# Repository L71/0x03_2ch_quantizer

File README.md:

0x03 2ch Quantizer
==================

This thing is a two channel CV quantizer for Eurorack, intended to make sure
some oscillators played by an analog sequencer are actually playing in tune :)

* two CV input channels, each input 0-5V is mapped to output 0-4.096V, four octaves @ 1V/oct.
* transpose knob per channel, +/- 1 octave in semitone steps
* The green LEDs will be brighter when transpose is set to -12/0/+12 half notes
* Red LED lights up if any channel tries to go off limits

Prototype build for Eurorack (complete with panel) was OK :) 

The microcontroller source code is released under the GPL v3.0 license. 
The PCBs and front panel drawings are released under the Creative Commons CC-BY-SA 4.0 license.

Tools used, all on MacOS 10.10:
C compiler: avr-gcc 4.3.3, http://www.obdev.at/products/crosspack/index.html
PCB: Eagle 7.1, www.cadsoftusa.com
Panel: Inkscape 0.91, inkscape.org

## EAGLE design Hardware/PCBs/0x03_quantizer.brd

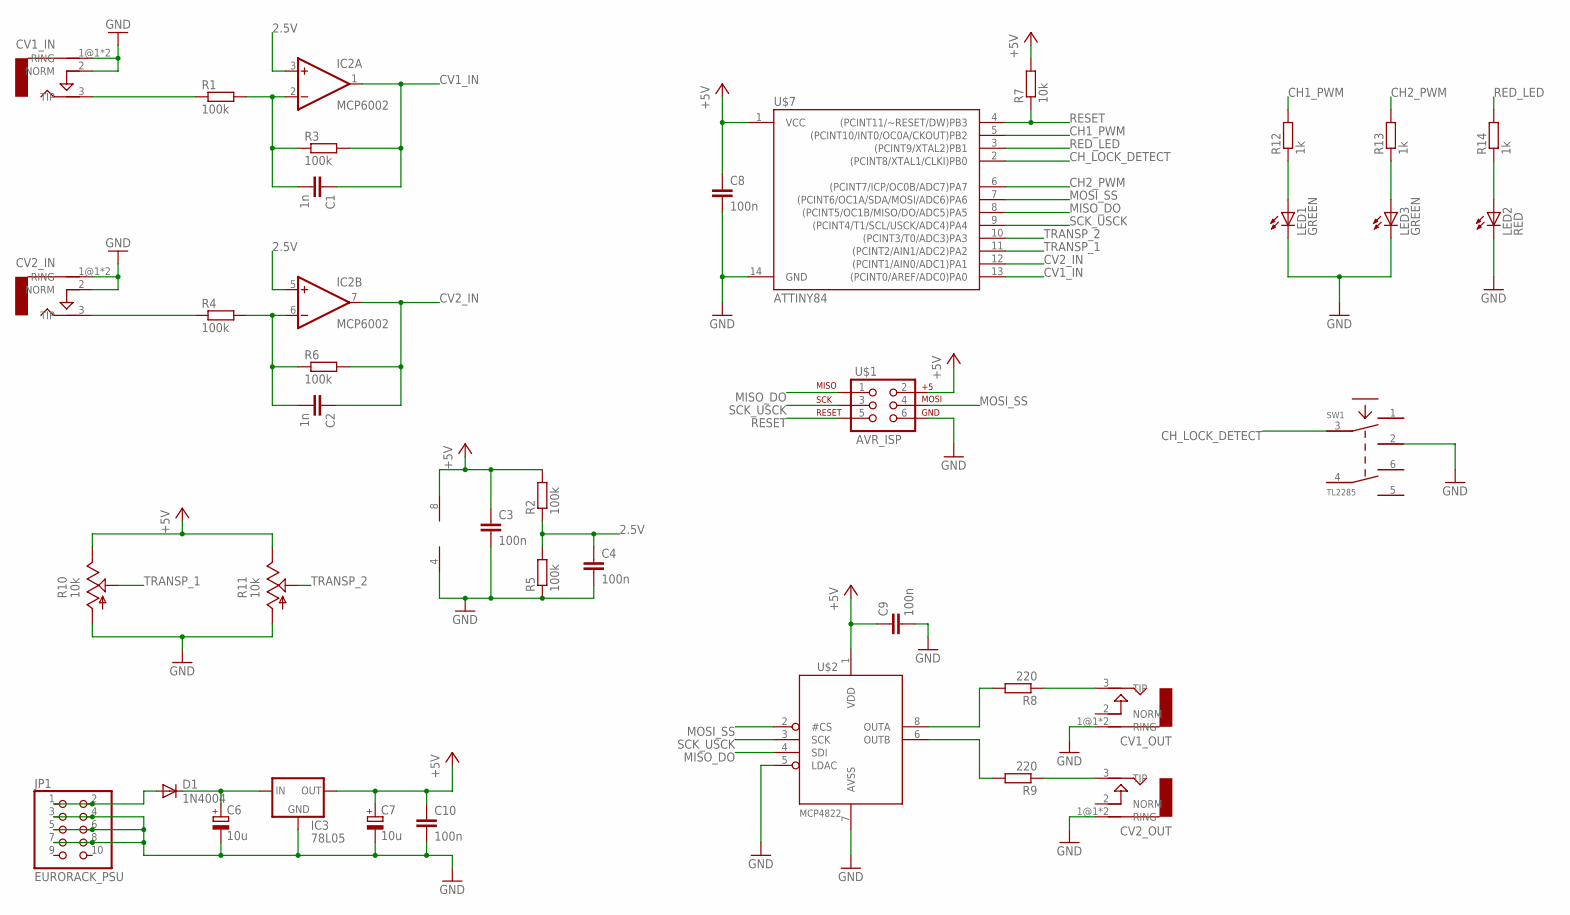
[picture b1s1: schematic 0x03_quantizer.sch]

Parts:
C1, C2: 1n; C025-025X050
C3, C4, C8, C9, C10: 100n; C025-025X050
C6, C7: 10u; E2,5-5
CV1_IN: CV1_IN; ERTHENVAR-JACK
CV1_OUT, CV2_OUT: AUDIO-JACKERTHENVAR; ERTHENVAR-JACK
CV2_IN: CV2_IN; ERTHENVAR-JACK
D1: 1N4004; DO41-10
IC2: MCP6002; DIL08
IC3: 78L05; 78LXX
JP1: EURORACK_PSU; 2X05
LED1, LED3: GREEN; LED5MM
LED2: RED; LED5MM
R1, R2, R3, R4, R5, R6: 100k; 0207/2V
R7: 10k; 0207/2V
R8, R9: 220; 0207/2V
R10, R11: 10k; ALPS_POT_VERTICAL
R12, R13, R14: 1k; 0207/2V
SW1: TL2285; TL2285_PCB
U$1: AVR_ISP; 2X3
U$2: MCP4822; DIL08
U$7: ATTINY84; DIL14

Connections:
2.5V: C4.1, IC2.3 (+IN), IC2.5 (+IN), R2.1, R5.2
12V: D1.A, JP1.1, JP1.2
+5V: C3.1, C7.+, C8.1, C9.1, C10.1, IC2.8 (V+), IC3.OUT, R2.2, R7.2, R10.P$1 (E), R11.P$1 (E), U$1.2, U$2.1 (VDD), U$7.1 (VCC)
AVSS: U$2.7 (AVSS)
CH1_PWM: R12.2, U$7.5 ((PCINT10/INT0/OC0A/CKOUT)PB2)
CH2_PWM: R13.2, U$7.6 ((PCINT7/ICP/OC0B/ADC7)PA7)
CH_LOCK_DETECT: SW1.3, U$7.2 ((PCINT8/XTAL1/CLKI)PB0)
CV1_IN: C1.1, IC2.1 (OUT), R3.2, U$7.13 ((PCINT0/AREF/ADC0)PA0)
CV2_IN: C2.1, IC2.7 (OUT), R6.2, U$7.12 ((PCINT1/AIN0/ADC1)PA1)
GND: C3.2, C4.2, C6.-, C7.-, C8.2, C9.2, C10.2, CV1_IN.1@1 (RING), CV1_IN.1@2 (RING), CV1_IN.2 (NORM), CV1_OUT.1@1 (RING), CV1_OUT.1@2 (RING), CV2_IN.1@1 (RING), CV2_IN.1@2 (RING), CV2_IN.2 (NORM), CV2_OUT.1@1 (RING), CV2_OUT.1@2 (RING), IC2.4 (V-), IC3.GND, JP1.3, JP1.4, JP1.5, JP1.6, JP1.7, JP1.8, LED1.K (C), LED2.K (C), LED3.K (C), R5.1, R10.P$3 (A), R11.P$3 (A), SW1.2, U$1.6, U$2.5 (LDAC), U$7.14 (GND)
MISO_DO: U$1.1, U$2.4 (SDI), U$7.8 ((PCINT5/OC1B/MISO/DO/ADC5)PA5)
MOSI_SS: U$1.4, U$2.2 (#CS), U$7.7 ((PCINT6/OC1A/SDA/MOSI/ADC6)PA6)
unnamed: C1.2, IC2.2 (-IN), R1.2, R3.1
unnamed: C6.+, D1.C, IC3.IN
unnamed: CV1_OUT.3 (TIP), R8.1
unnamed: CV1_IN.3 (TIP), R1.1
unnamed: CV2_OUT.3 (TIP), R9.1
unnamed: R9.2, U$2.6 (OUTB)
unnamed: C2.2, IC2.6 (-IN), R4.2, R6.1
unnamed: LED2.A, R14.1
unnamed: CV2_IN.3 (TIP), R4.1
unnamed: R8.2, U$2.8 (OUTA)
unnamed: LED3.A, R13.1
unnamed: LED1.A, R12.1
RED_LED: R14.2, U$7.3 ((PCINT9/XTAL2)PB1)
RESET: R7.1, U$1.5, U$7.4 ((PCINT11/~RESET/DW)PB3)
SCK_USCK: U$1.3, U$2.3 (SCK), U$7.9 ((PCINT4/T1/SCL/USCK/ADC4)PA4)
TRANSP_1: R10.P$2 (S), U$7.11 ((PCINT2/AIN1/ADC2)PA2)
TRANSP_2: R11.P$2 (S), U$7.10 ((PCINT3/T0/ADC3)PA3)

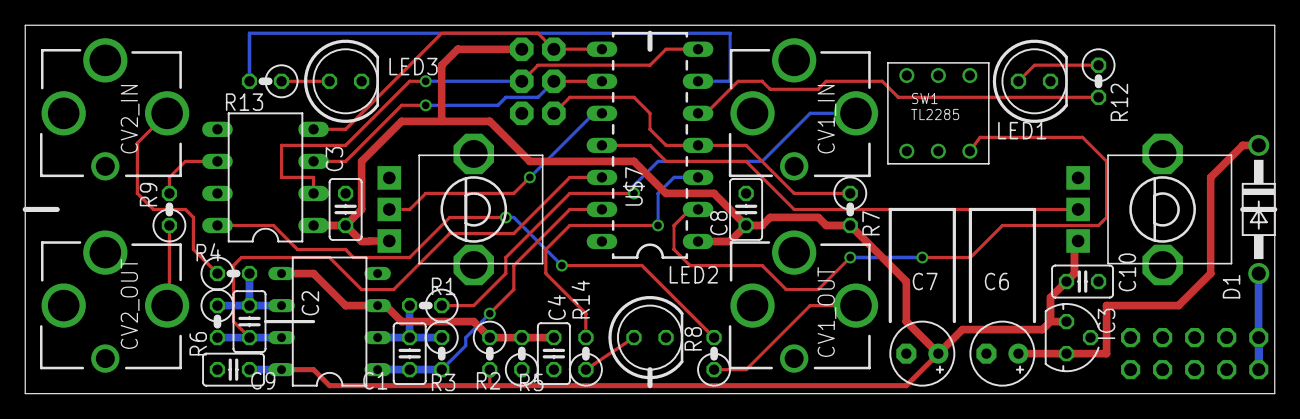
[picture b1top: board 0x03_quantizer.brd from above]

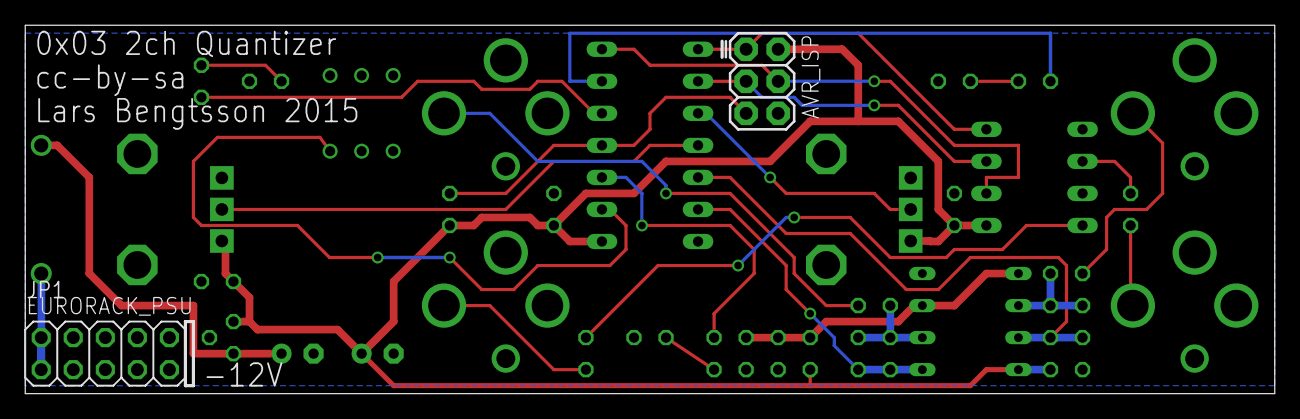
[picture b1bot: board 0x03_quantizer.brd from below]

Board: 2 copper layers, 99.1 x 29.2 mm, 38 parts (2 on the bottom side), 28 nets.

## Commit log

2015-02-09 Added gitignore file.
2015-02-09 Added makefile(s).
2015-02-15 Initial upload of (it appears) working code :)
2015-02-15 Initial upload of PCB files.
2015-02-15 Initial upload of README.
2015-02-15 Corected speling mistaek.
2015-02-18 Initial version of panel.
2015-02-19 Final version for first order (no LED holes, for transparent panel).
2015-02-19 Ponoko P1 template, 6 panels.
2015-02-27 Front panel file with 5mm holes for LEDs. Use for opaque panels.
2015-03-05 Updated after first prototype build.
2015-03-25 Updated: No fill in text, just outlines, and holes for 5mm LEDs.
2015-03-25 Missed to change one hole. Corrected.

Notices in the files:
parts and their libraries:
SparkFun-DigitalIC: Licensing: Creative Commons ShareAlike 4.0 International - https://creativecommons.org/licenses/by-sa/4.0
